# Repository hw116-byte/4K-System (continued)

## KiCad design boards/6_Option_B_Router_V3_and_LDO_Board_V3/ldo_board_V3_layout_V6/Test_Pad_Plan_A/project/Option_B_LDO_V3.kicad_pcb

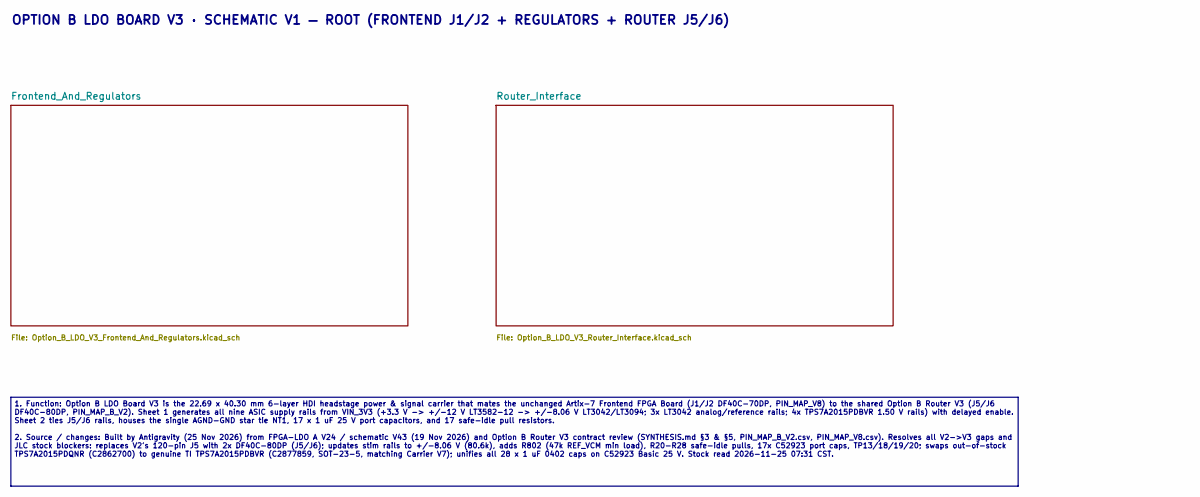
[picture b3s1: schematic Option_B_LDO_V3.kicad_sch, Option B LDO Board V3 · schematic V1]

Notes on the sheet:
1. Function: Option B LDO Board V3 is the 22.69 x 40.30 mm 6-layer HDI headstage power & signal carrier that mates the unchanged Artix-7 Frontend FPGA Board (J1/J2 DF40C-70DP, PIN_MAP_V8) to the shared Option B Router V3 (J5/J6 DF40C-80DP, PIN_MAP_B_V2). Sheet 1 generates all nine ASIC supply rails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
OPTION B LDO BOARD V3 · SCHEMATIC V1 — ROOT (FRONTEND J1/J2 + REGULATORS + ROUTER J5/J6)

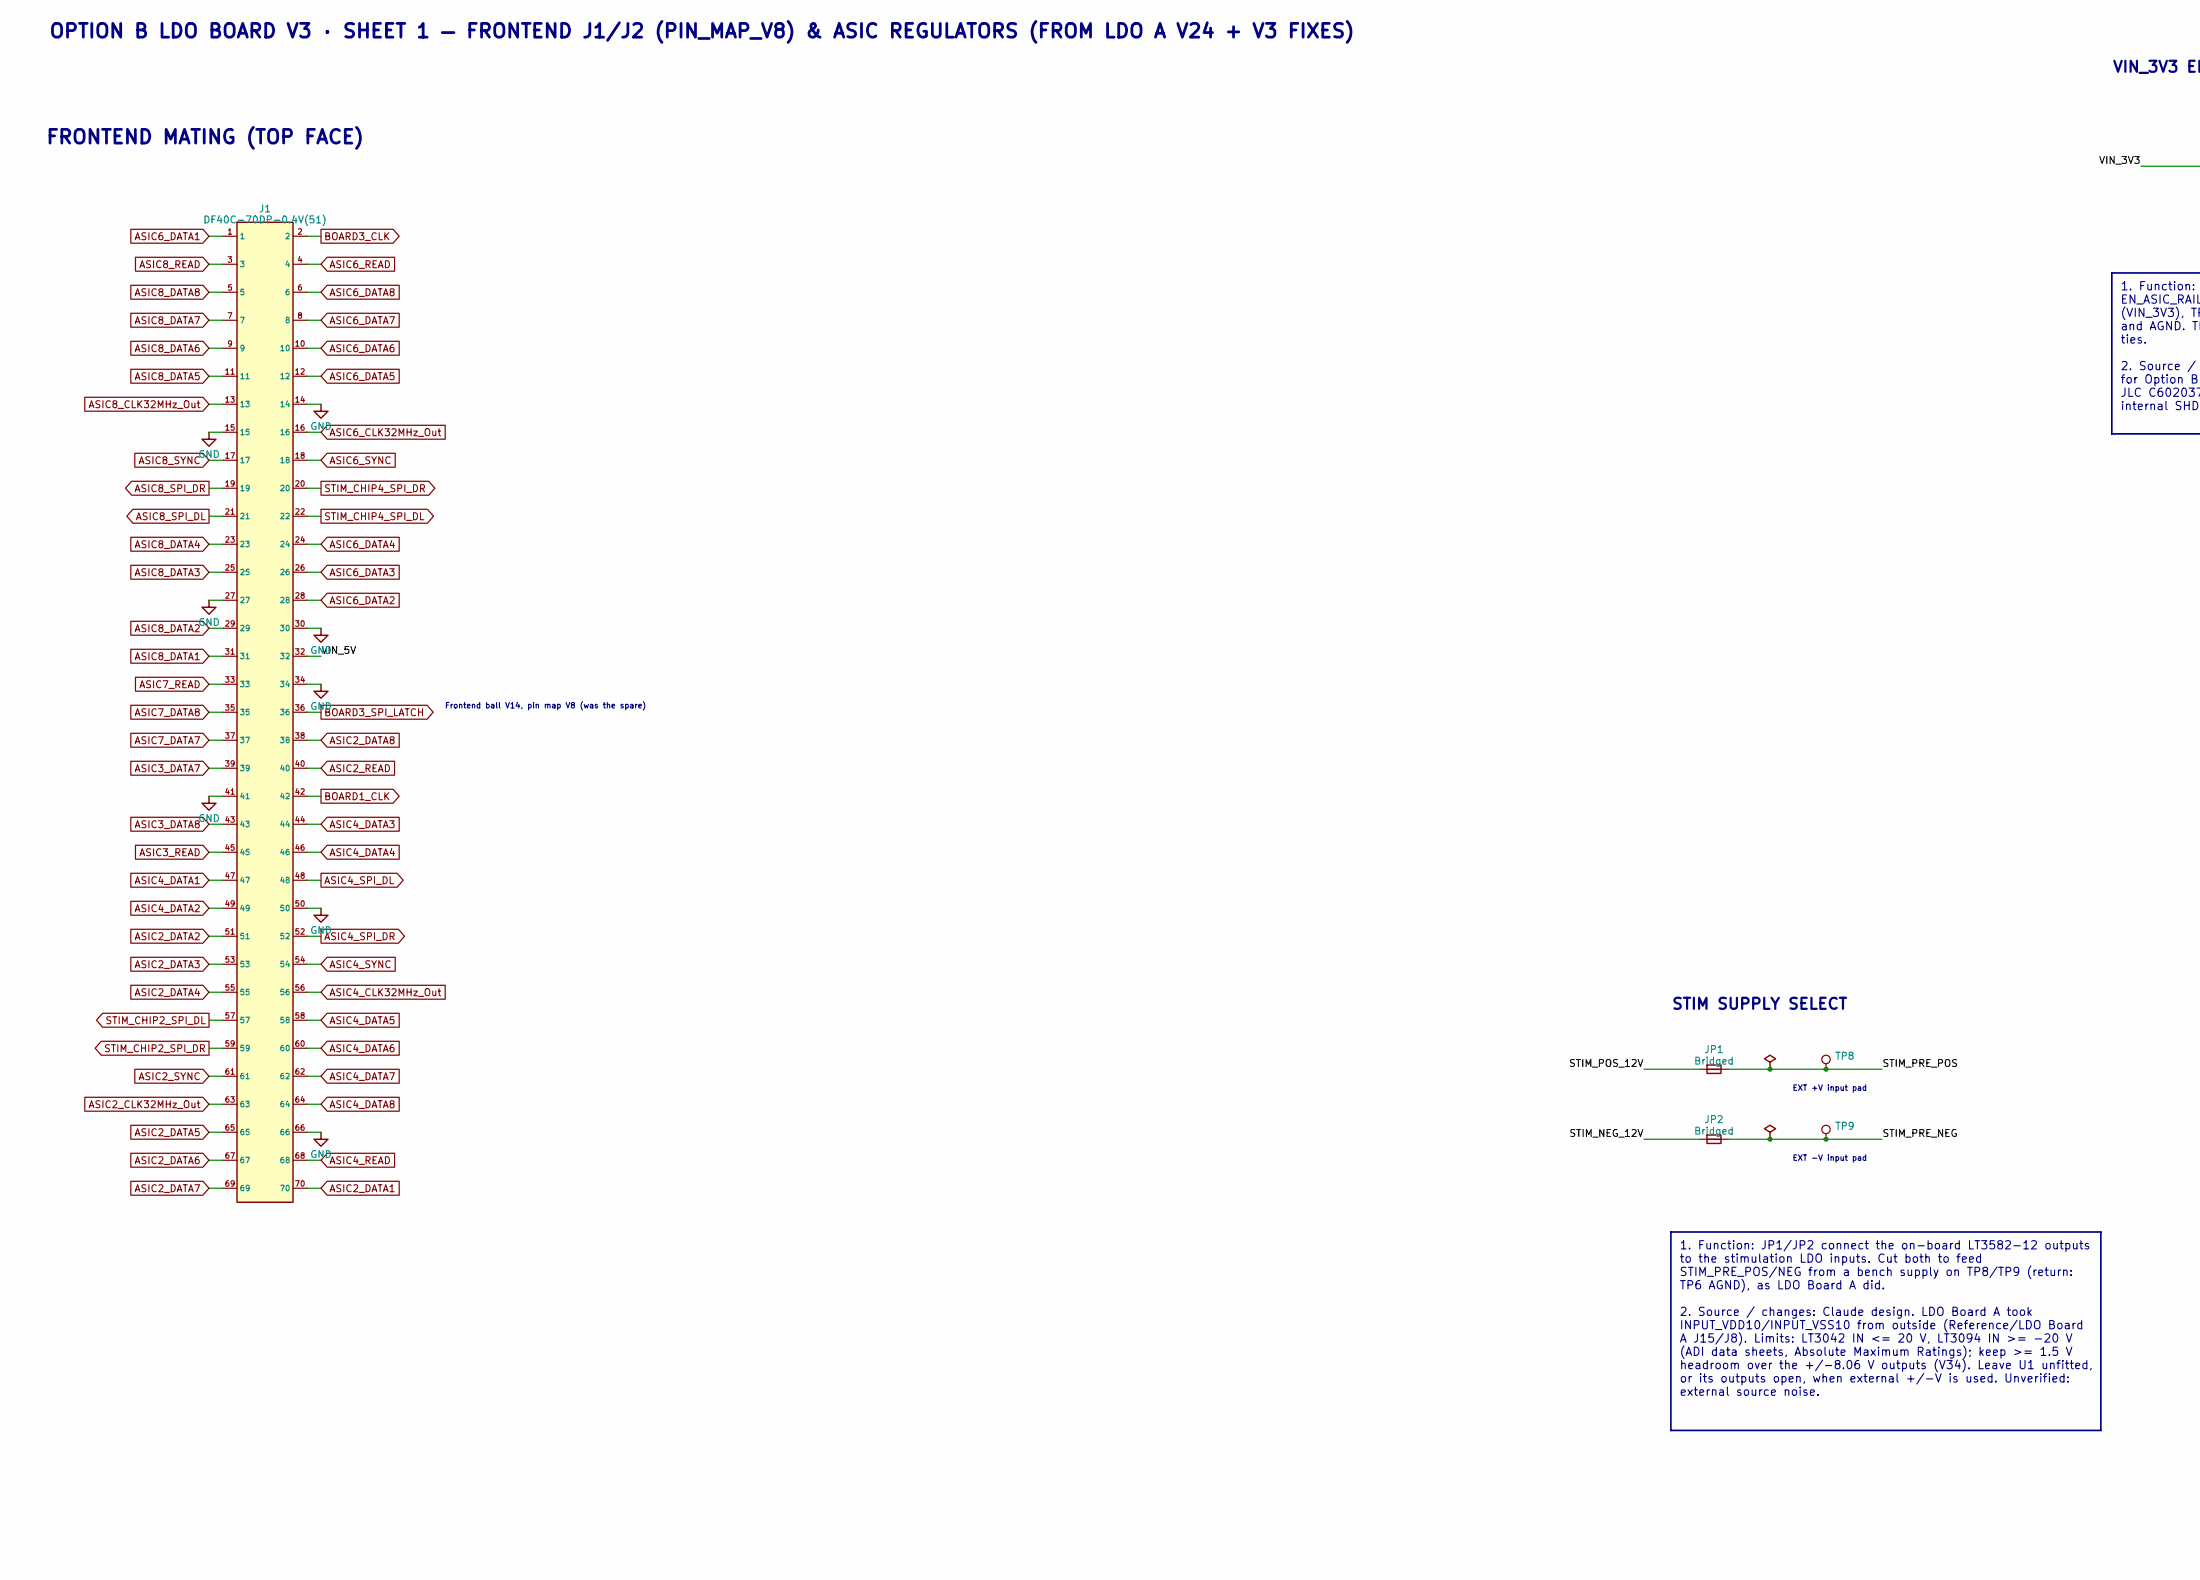
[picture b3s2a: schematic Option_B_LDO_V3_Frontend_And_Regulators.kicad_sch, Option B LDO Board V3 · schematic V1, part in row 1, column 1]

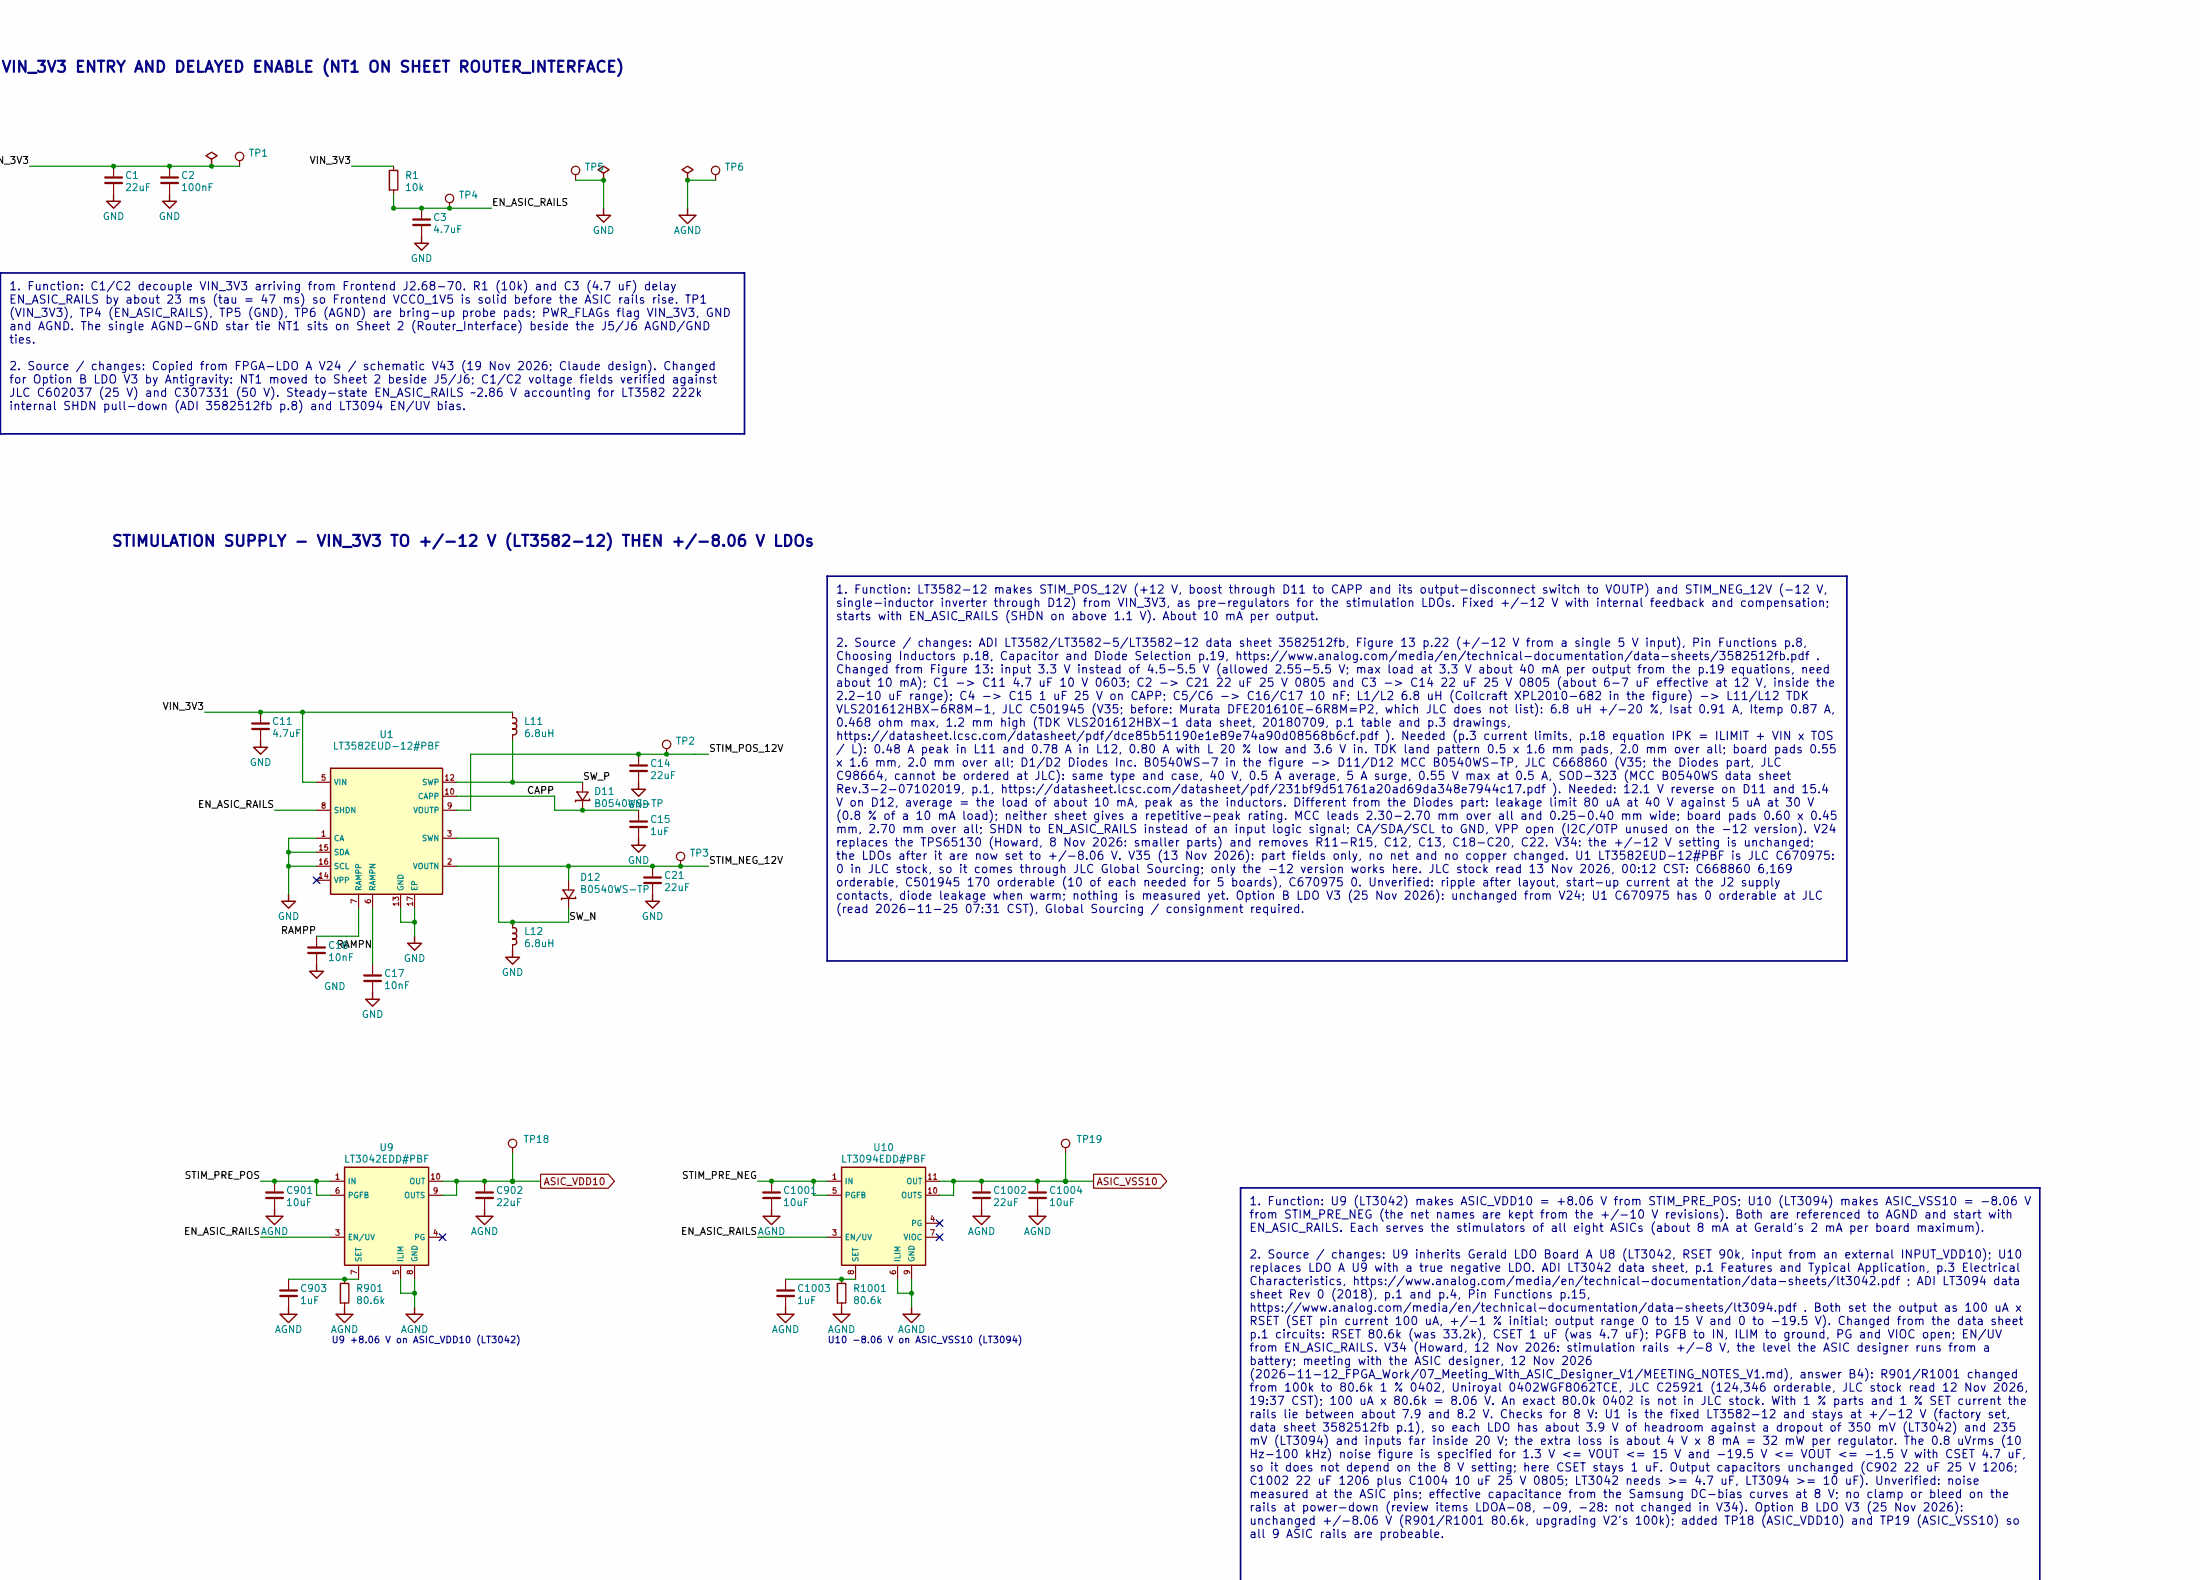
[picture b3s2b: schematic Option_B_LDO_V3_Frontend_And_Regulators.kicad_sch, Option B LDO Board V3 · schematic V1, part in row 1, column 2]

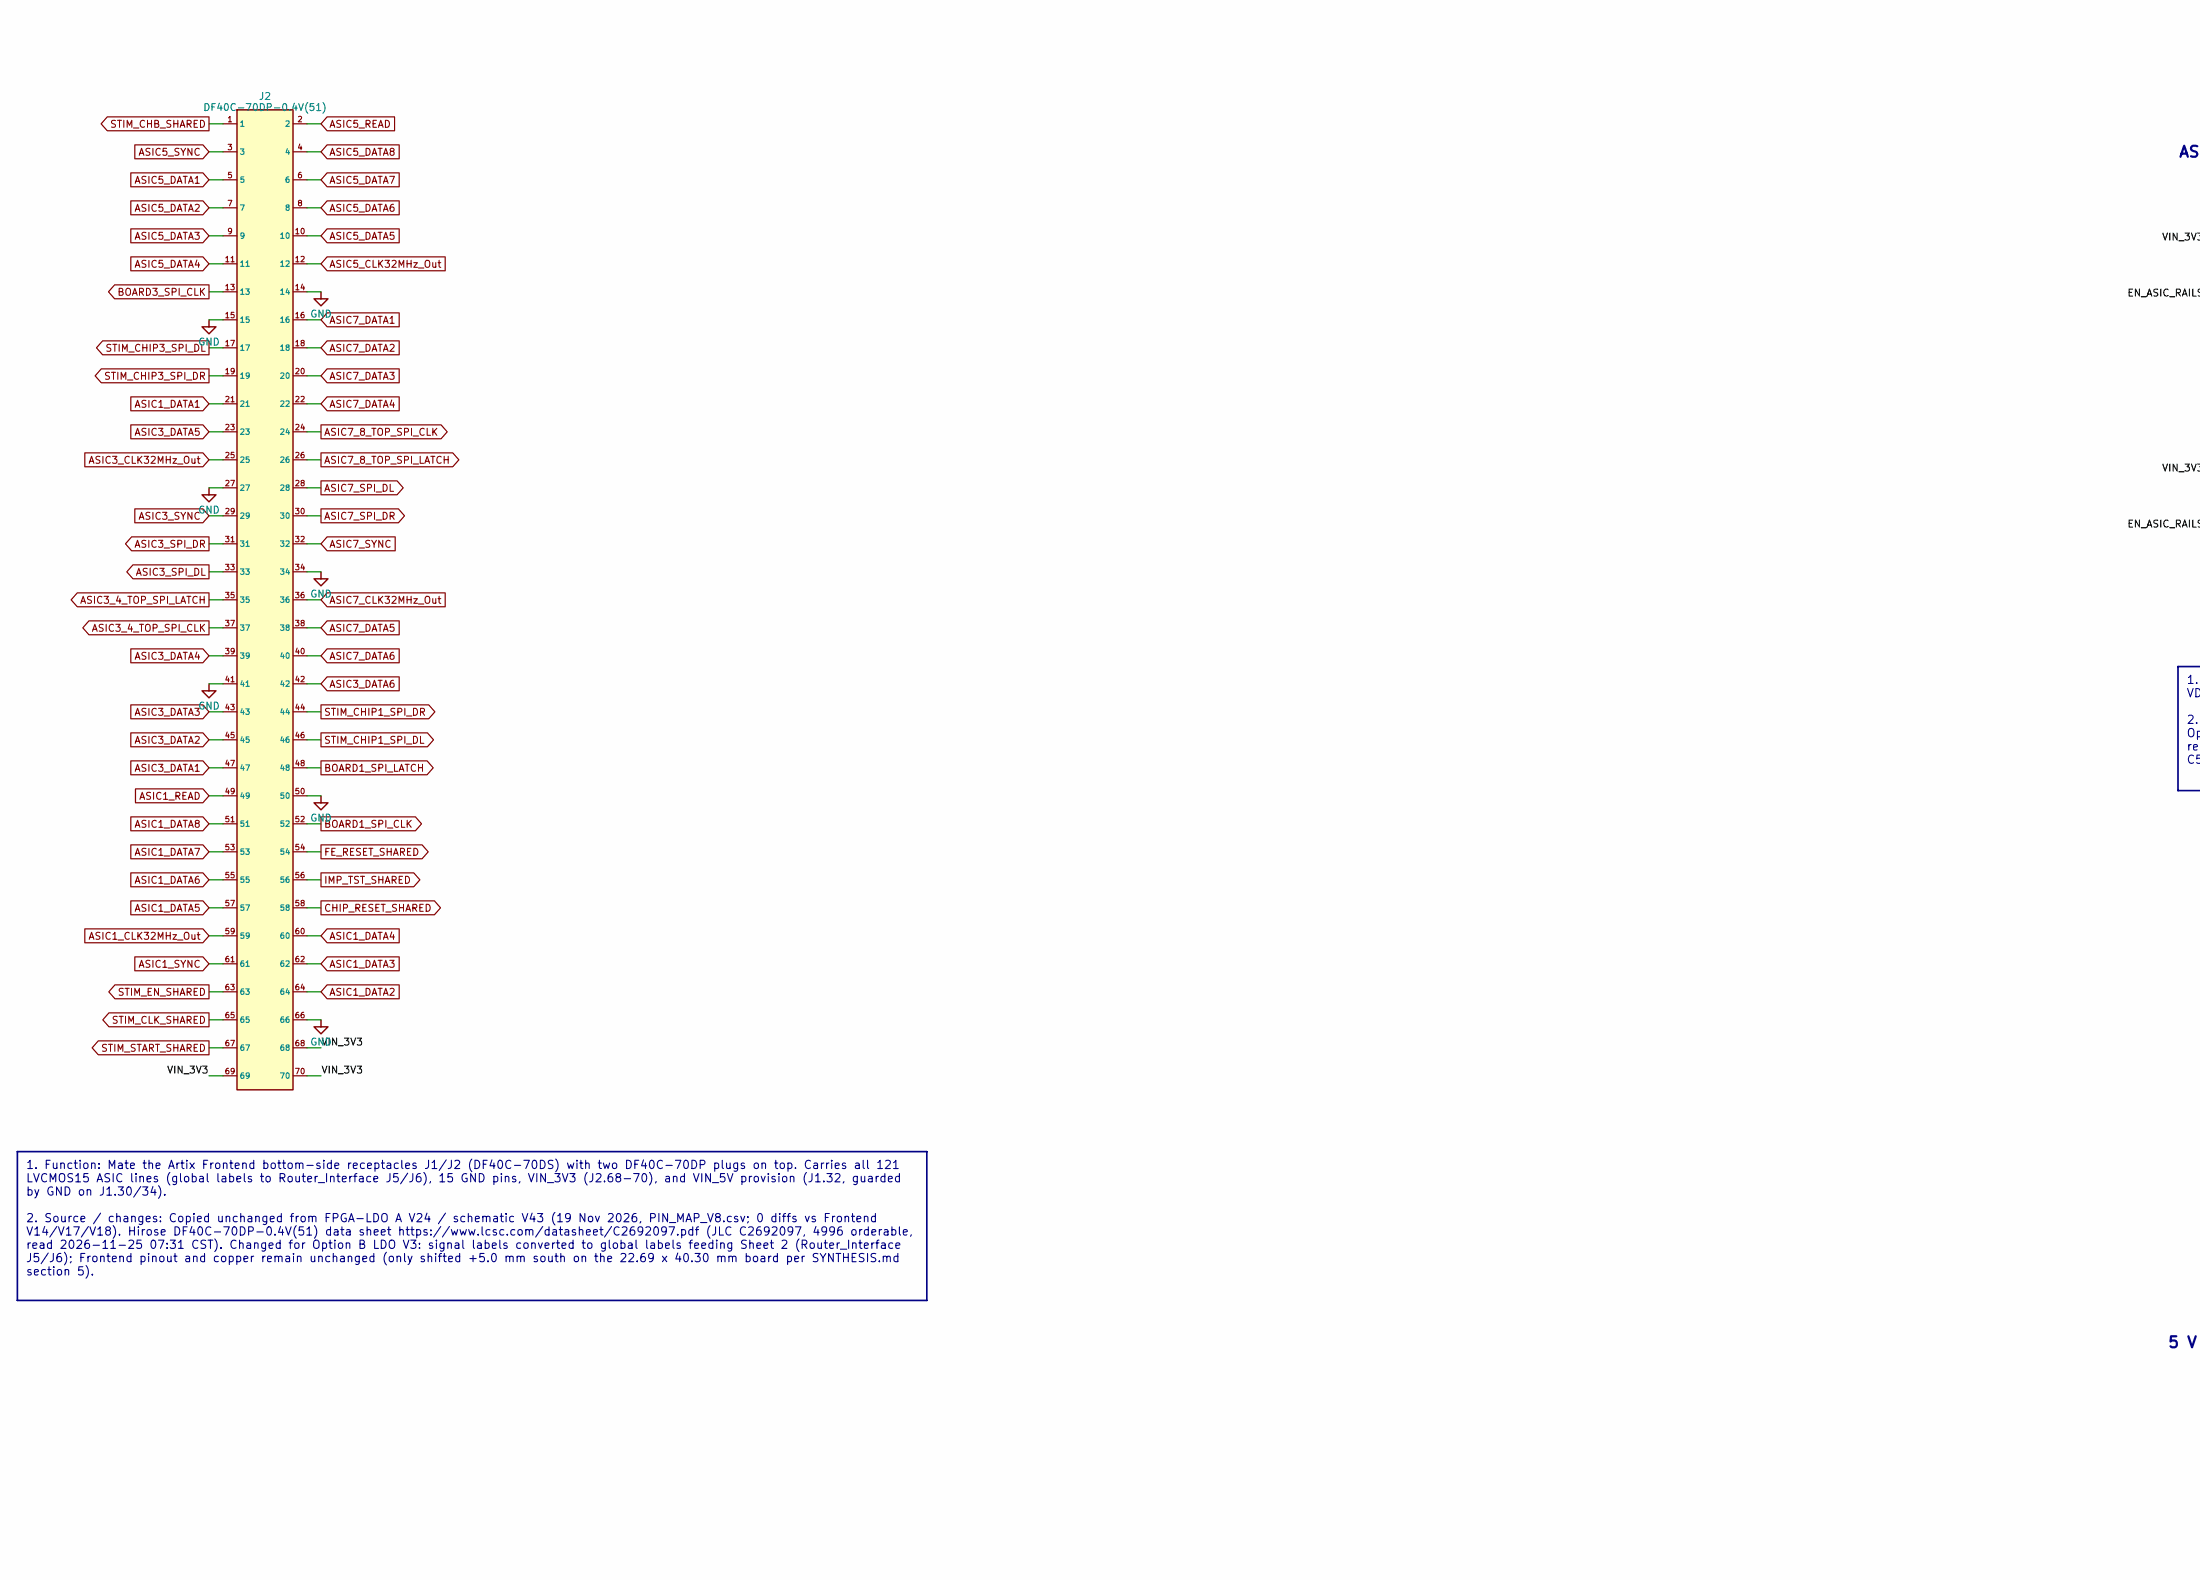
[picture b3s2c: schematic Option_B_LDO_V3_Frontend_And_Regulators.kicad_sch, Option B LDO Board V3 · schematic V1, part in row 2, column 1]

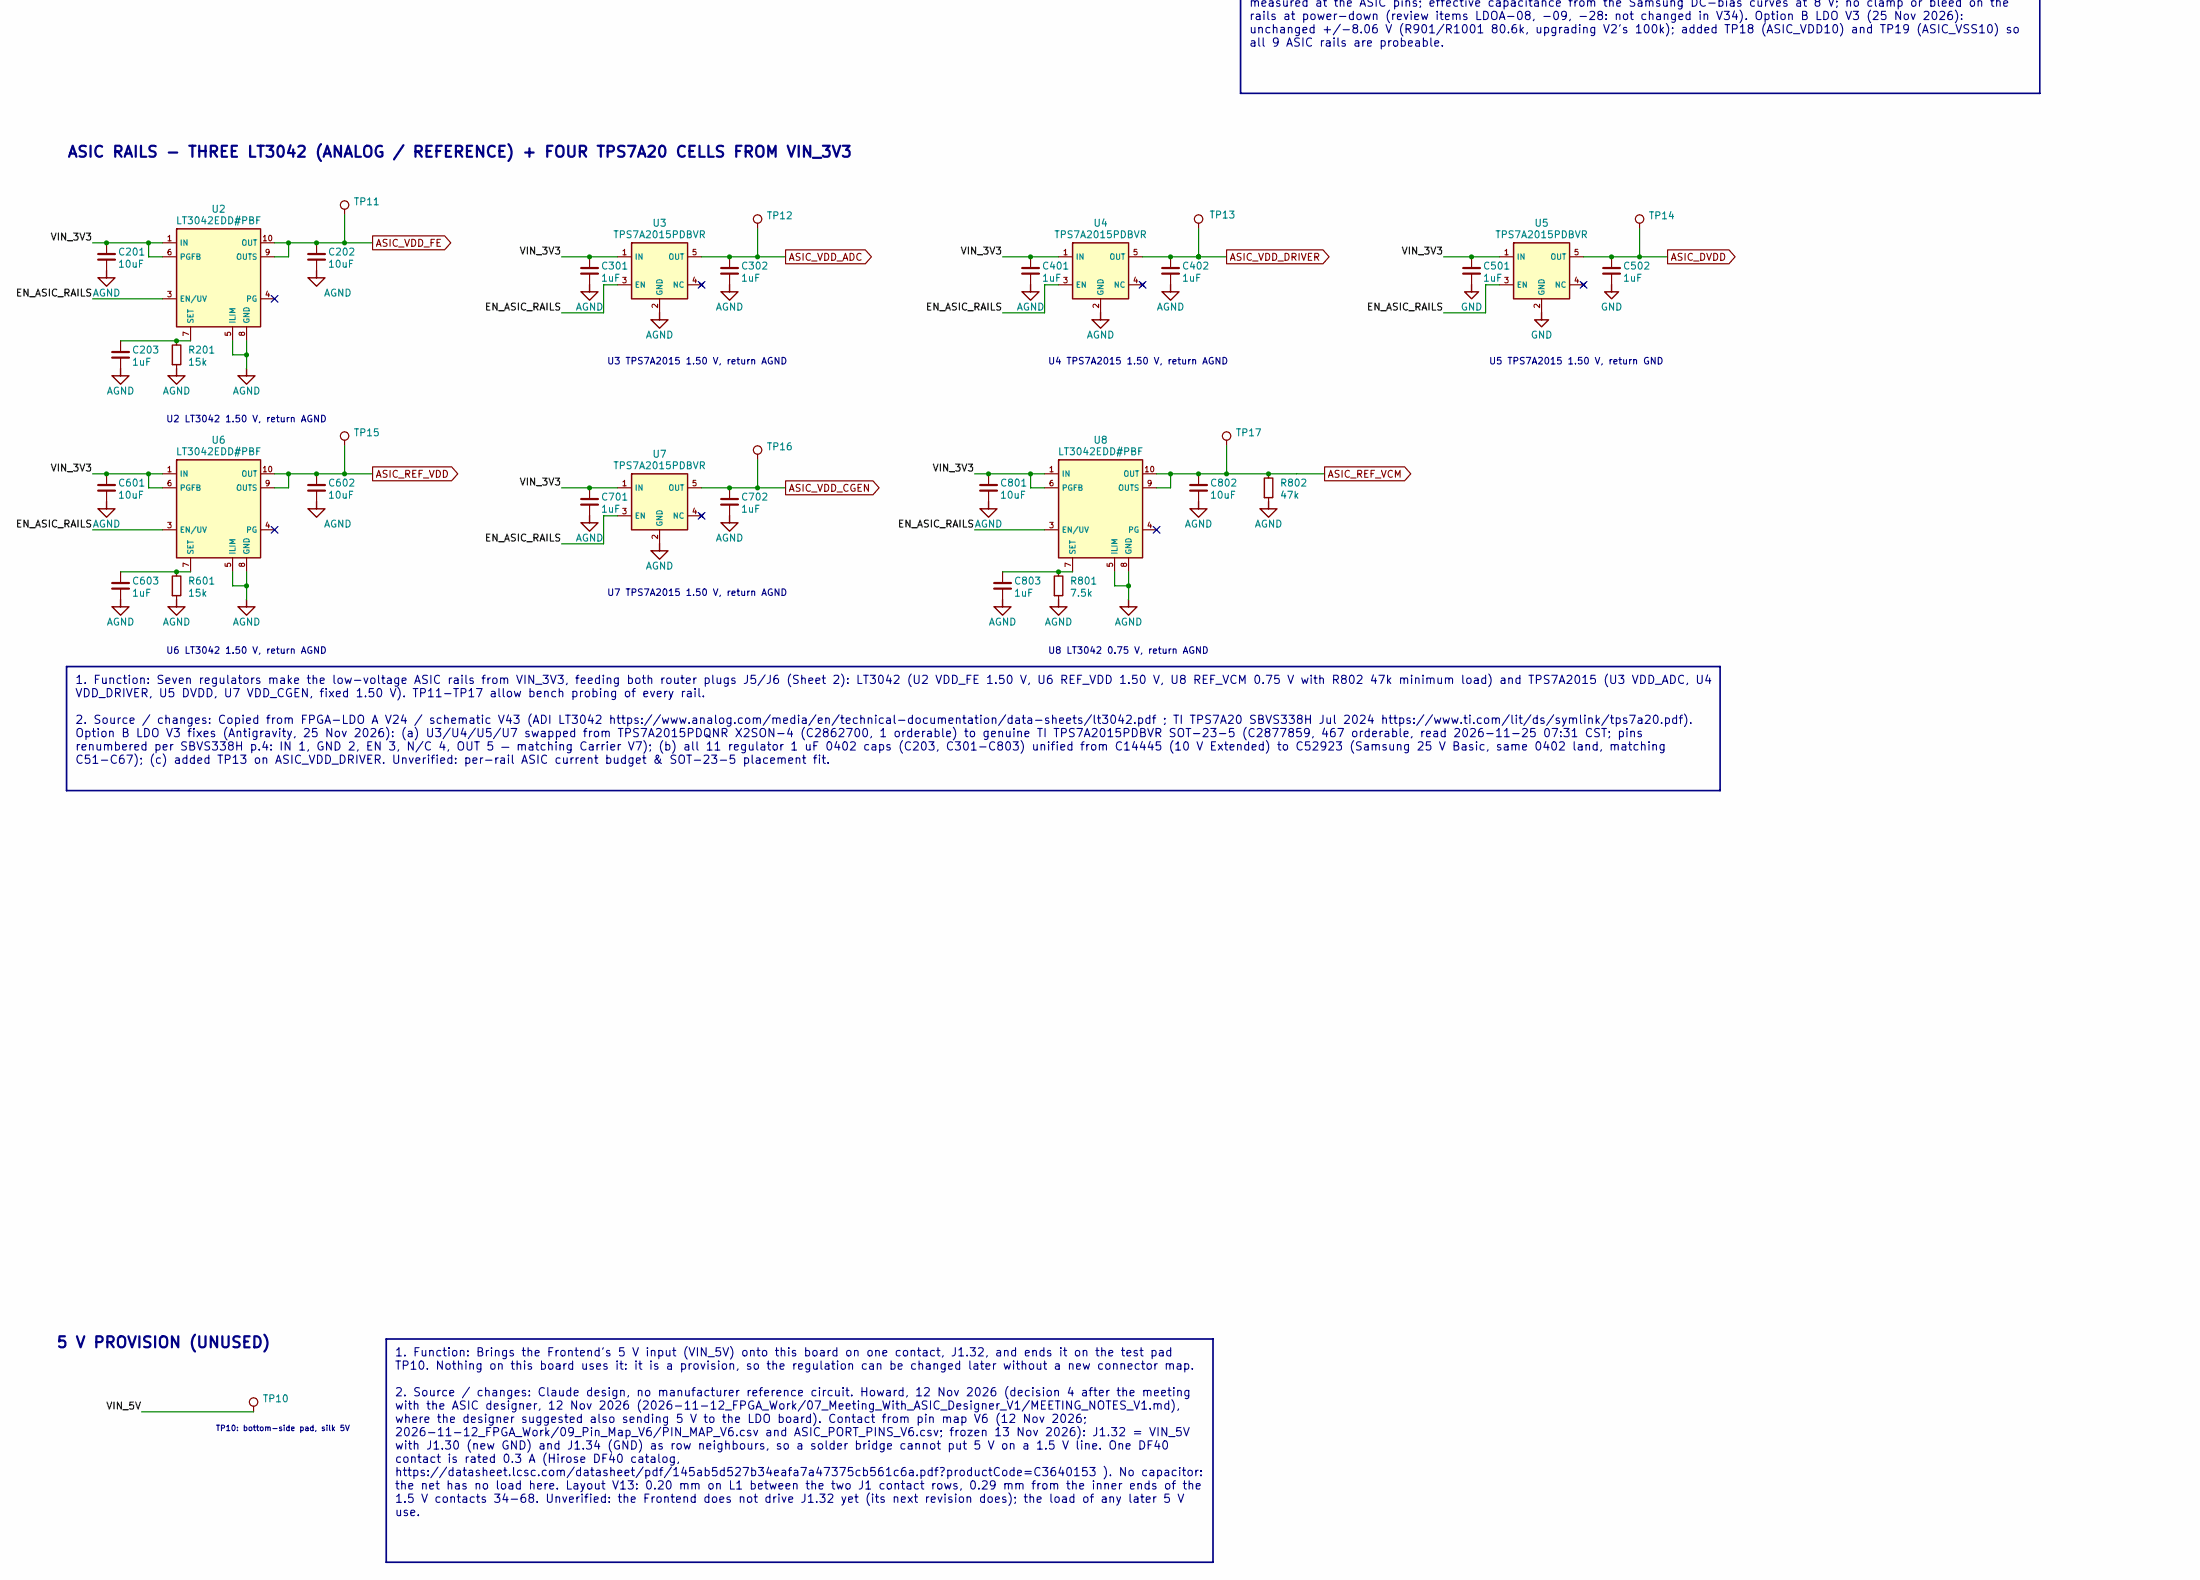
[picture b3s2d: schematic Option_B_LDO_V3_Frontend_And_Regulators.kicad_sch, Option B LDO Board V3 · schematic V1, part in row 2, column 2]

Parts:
C1, C14, C21: 22uF; C_0805_2012Metric; Voltage 25V; MPN Samsung CL21A226MAYNNNE (22uF 25V X5R 0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; LCSC C602037
C2: 100nF; C_0402_1005Metric; Voltage 50V; MPN Samsung CL05B104KB54PNC (100nF 50V X7R 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; LCSC C307331
C3: 4.7uF; C_0603_1608Metric; Voltage 10V; MPN Samsung CL10A475KP8NNNC (4.7uF 10V X5R 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; LCSC C1705
C11: 4.7uF; C_0603_1608Metric; Voltage 10V; LCSC C1705
C15, C903, C1003: 1uF; C_0603_1608Metric; Voltage 25V; MPN Samsung CL10A105KA8NNNC (1uF 25V X5R 06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; LCSC C5673
C16, C17: 10nF; C_0402_1005Metric; Voltage 50V; MPN Samsung CL05B103KB5NNNC (10nF 50V X7R 0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; LCSC C15195
C201, C202, C601, C602, C801, C802: 10uF; C_0603_1608Metric; Voltage 10V; MPN Samsung CL10A106KP8NNNC (10uF 10V X5R 0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; LCSC C19702
C203, C301, C302, C401, C402, C501, C502, C603, C701, C702, C803: 1uF; C_0402_1005Metric; Voltage 25V; MPN Samsung CL05A105KA5NQNC (1 uF 25 V X5R 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; LCSC C52923
C901, C1001, C1004: 10uF; C_0805_2012Metric; Voltage 25V; MPN Samsung CL21A106KAYNNNE (10uF 25V X5R 0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; LCSC C15850
C902, C1002: 22uF; C_1206_3216Metric; Voltage 25V; MPN Samsung CL31A226KAHNNNE (22uF 25V X5R 1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; LCSC C12891
D11, D12: B0540WS-TP; D_SOD-323; MPN MCC B0540WS-TP (40 V 0.5 A SOD-323); LCSC C668860
J1, J2: DF40C-70DP-0.4V(51); Hirose_DF40C-70DP-0.4V_2x35-1MP_P0.4mm; MPN DF40C-70DP-0.4V(51); LCSC C2692097
JP1, JP2: Bridged; SolderJumper-2_P1.3mm_Bridged_RoundedPad1.0x1.5mm
L11, L12: 6.8uH; L_Murata_DFE201610P; MPN TDK VLS201612HBX-6R8M-1 (6.8 uH 20 %, 2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; LCSC C501945
R1: 10k; R_0402_1005Metric; Tolerance 1%; LCSC C25744
R201, R601: 15k; R_0402_1005Metric; Tolerance 1%; MPN UNI-ROYAL 0402WGF1502TCE (15k 1% 0402); LCSC C25756
R801: 7.5k; R_0402_1005Metric; Tolerance 1%; MPN UNI-ROYAL 0402WGF7501TCE (7.5k 1% 0402); LCSC C25918
R802: 47k; R_0402_1005Metric; Tolerance 1%; MPN Uniroyal 0402WGF4702TCE (47k 1% 0402); LCSC C25792
R901, R1001: 80.6k; R_0402_1005Metric; Tolerance 1%; MPN Uniroyal 0402WGF8062TCE (80.6k 1% 0402); LCSC C25921
TP1: VIN_3V3; TestPoint_Pad_D1.0mm_Compact
TP2: STIM_POS_12V; TestPoint_Pad_D1.0mm_Compact
TP3: STIM_NEG_12V; TestPoint_Pad_D1.0mm_Compact
TP4: EN_ASIC_RAILS; TestPoint_Pad_D1.0mm_Compact
TP5: GND; TestPoint_Pad_D1.0mm_Compact
TP6: AGND; TestPoint_Pad_D1.0mm_Compact
TP8: STIM_PRE_POS; TestPoint_Pad_D1.0mm_Compact
TP9: STIM_PRE_NEG; TestPoint_Pad_D1.0mm_Compact
TP10: VIN_5V; TestPoint_Pad_D1.0mm_Compact
TP11: ASIC_VDD_FE; TestPoint_Pad_D0.6mm_Compact
TP12: ASIC_VDD_ADC; TestPoint_Pad_D0.6mm_Compact
TP13: ASIC_VDD_DRIVER; TestPoint_Pad_D1.0mm_Compact
TP14: ASIC_DVDD; TestPoint_Pad_D0.6mm_Compact
TP15: ASIC_REF_VDD; TestPoint_Pad_D0.6mm_Compact
TP16: ASIC_VDD_CGEN; TestPoint_Pad_D0.6mm_Compact
TP17: ASIC_REF_VCM; TestPoint_Pad_D0.6mm_Compact
TP18: ASIC_VDD10; TestPoint_Pad_D1.0mm_Compact
TP19: ASIC_VSS10; TestPoint_Pad_D1.0mm_Compact
U1: LT3582EUD-12#PBF; QFN-16-1EP_3x3mm_P0.5mm_EP1.45x1.45mm; MPN LT3582EUD-12#PBF; LCSC C670975
U2, U6, U8, U9: LT3042EDD#PBF; DFN-10-1EP_3x3mm_P0.5mm_EP1.65x2.38mm; MPN LT3042EDD#TRPBF; LCSC C580010
U3, U4, U5, U7: TPS7A2015PDBVR; SOT-23-5; MPN TPS7A2015PDBVR; LCSC C2877859
U10: LT3094EDD#PBF; DFN-12-1EP_3x3mm_P0.45mm_EP1.65x2.38mm; MPN LT3094EDD#PBF; LCSC C670492

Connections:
/Frontend_And_Regulators/CAPP: C15.1, D11.1 (K), U1.10 (CAPP), U1.11 (CAPP)
/Frontend_And_Regulators/EN_ASIC_RAILS: C3.1, R1.2, TP4.1, U1.8 (SHDN), U2.3 (EN/UV), U3.3 (EN), U4.3 (EN), U5.3 (EN), U6.3 (EN/UV), U7.3 (EN), U8.3 (EN/UV), U9.3 (EN/UV), U10.3 (EN/UV)
/Frontend_And_Regulators/RAMPN: C17.1, U1.6 (RAMPN)
/Frontend_And_Regulators/RAMPP: C16.1, U1.7 (RAMPP)
/Frontend_And_Regulators/STIM_NEG_12V: C21.1, D12.2 (A), JP2.1, TP3.1, U1.2 (VOUTN)
/Frontend_And_Regulators/STIM_POS_12V: C14.1, JP1.1, TP2.1, U1.9 (VOUTP)
/Frontend_And_Regulators/STIM_PRE_NEG: C1001.1, JP2.2, TP9.1, U10.1 (IN), U10.2 (IN), U10.5 (PGFB), U10.13 (IN)
/Frontend_And_Regulators/STIM_PRE_POS: C901.1, JP1.2, TP8.1, U9.1 (IN), U9.2 (IN), U9.6 (PGFB)
/Frontend_And_Regulators/SW_N: D12.1 (K), L12.1, U1.3 (SWN), U1.4 (SWN)
/Frontend_And_Regulators/SW_P: D11.2 (A), L11.2, U1.12 (SWP)
/Frontend_And_Regulators/VIN_3V3: C1.1, C2.1, C11.1, C201.1, C301.1, C401.1, C501.1, C601.1, C701.1, C801.1, J2.68, J2.69, J2.70, L11.1, R1.1, TP1.1, U1.5 (VIN), U2.1 (IN), U2.2 (IN), U2.6 (PGFB), U3.1 (IN), U4.1 (IN), U5.1 (IN), U6.1 (IN), U6.2 (IN), U6.6 (PGFB), U7.1 (IN), U8.1 (IN), U8.2 (IN), U8.6 (PGFB)
/Frontend_And_Regulators/VIN_5V: J1.32, TP10.1
AGND: C201.2, C202.2, C203.2, C301.2, C302.2, C401.2, C402.2, C601.2, C602.2, C603.2, C701.2, C702.2, C801.2, C802.2, C803.2, C901.2, C902.2, C903.2, C1001.2, C1002.2, C1003.2, C1004.2, R201.2, R601.2, R801.2, R802.2, R901.2, R1001.2, TP6.1, U2.5 (ILIM), U2.8 (GND), U2.11 (GND), U3.2 (GND), U4.2 (GND), U6.5 (ILIM), U6.8 (GND), U6.11 (GND), U7.2 (GND), U8.5 (ILIM), U8.8 (GND), U8.11 (GND), U9.5 (ILIM), U9.8 (GND), U9.11 (GND), U10.6 (ILIM), U10.9 (GND); also elsewhere on the board
ASIC1_CLK32MHz_Out: J2.59; also elsewhere on the board
ASIC1_DATA1: J2.21; also elsewhere on the board
ASIC1_DATA2: J2.64; also elsewhere on the board
ASIC1_DATA3: J2.62; also elsewhere on the board
ASIC1_DATA4: J2.60; also elsewhere on the board
ASIC1_DATA5: J2.57; also elsewhere on the board
ASIC1_DATA6: J2.55; also elsewhere on the board
ASIC1_DATA7: J2.53; also elsewhere on the board
ASIC1_DATA8: J2.51; also elsewhere on the board
ASIC1_READ: J2.49; also elsewhere on the board
ASIC1_SYNC: J2.61; also elsewhere on the board
ASIC2_CLK32MHz_Out: J1.63; also elsewhere on the board
ASIC2_DATA1: J1.70; also elsewhere on the board
ASIC2_DATA2: J1.51; also elsewhere on the board
ASIC2_DATA3: J1.53; also elsewhere on the board
ASIC2_DATA4: J1.55; also elsewhere on the board
ASIC2_DATA5: J1.65; also elsewhere on the board
ASIC2_DATA6: J1.67; also elsewhere on the board
ASIC2_DATA7: J1.69; also elsewhere on the board
ASIC2_DATA8: J1.38; also elsewhere on the board
ASIC2_READ: J1.40; also elsewhere on the board
ASIC2_SYNC: J1.61; also elsewhere on the board
ASIC3_4_TOP_SPI_CLK: J2.37; also elsewhere on the board
ASIC3_4_TOP_SPI_LATCH: J2.35; also elsewhere on the board
ASIC3_CLK32MHz_Out: J2.25; also elsewhere on the board
ASIC3_DATA1: J2.47; also elsewhere on the board
ASIC3_DATA2: J2.45; also elsewhere on the board
ASIC3_DATA3: J2.43; also elsewhere on the board
ASIC3_DATA4: J2.39; also elsewhere on the board
ASIC3_DATA5: J2.23; also elsewhere on the board
ASIC3_DATA6: J2.42; also elsewhere on the board
ASIC3_DATA7: J1.39; also elsewhere on the board
ASIC3_DATA8: J1.43; also elsewhere on the board
ASIC3_READ: J1.45; also elsewhere on the board
ASIC3_SPI_DL: J2.33; also elsewhere on the board
ASIC3_SPI_DR: J2.31; also elsewhere on the board
ASIC3_SYNC: J2.29; also elsewhere on the board
ASIC4_CLK32MHz_Out: J1.56; also elsewhere on the board
ASIC4_DATA1: J1.47; also elsewhere on the board
ASIC4_DATA2: J1.49; also elsewhere on the board
ASIC4_DATA3: J1.44; also elsewhere on the board
ASIC4_DATA4: J1.46; also elsewhere on the board
ASIC4_DATA5: J1.58; also elsewhere on the board
ASIC4_DATA6: J1.60; also elsewhere on the board
ASIC4_DATA7: J1.62; also elsewhere on the board
ASIC4_DATA8: J1.64; also elsewhere on the board
ASIC4_READ: J1.68; also elsewhere on the board
ASIC4_SPI_DL: J1.48; also elsewhere on the board
ASIC4_SPI_DR: J1.52; also elsewhere on the board
ASIC4_SYNC: J1.54; also elsewhere on the board
ASIC5_CLK32MHz_Out: J2.12; also elsewhere on the board
ASIC5_DATA1: J2.5; also elsewhere on the board
ASIC5_DATA2: J2.7; also elsewhere on the board
ASIC5_DATA3: J2.9; also elsewhere on the board
ASIC5_DATA4: J2.11; also elsewhere on the board
ASIC5_DATA5: J2.10; also elsewhere on the board
ASIC5_DATA6: J2.8; also elsewhere on the board
ASIC5_DATA7: J2.6; also elsewhere on the board
ASIC5_DATA8: J2.4; also elsewhere on the board
ASIC5_READ: J2.2; also elsewhere on the board
ASIC5_SYNC: J2.3; also elsewhere on the board
ASIC6_CLK32MHz_Out: J1.16; also elsewhere on the board
ASIC6_DATA1: J1.1; also elsewhere on the board
ASIC6_DATA2: J1.28; also elsewhere on the board
ASIC6_DATA3: J1.26; also elsewhere on the board
ASIC6_DATA4: J1.24; also elsewhere on the board
ASIC6_DATA5: J1.12; also elsewhere on the board
ASIC6_DATA6: J1.10; also elsewhere on the board
ASIC6_DATA7: J1.8; also elsewhere on the board
ASIC6_DATA8: J1.6; also elsewhere on the board
ASIC6_READ: J1.4; also elsewhere on the board
ASIC6_SYNC: J1.18; also elsewhere on the board
ASIC7_8_TOP_SPI_CLK: J2.24; also elsewhere on the board
ASIC7_8_TOP_SPI_LATCH: J2.26; also elsewhere on the board
ASIC7_CLK32MHz_Out: J2.36; also elsewhere on the board
ASIC7_DATA1: J2.16; also elsewhere on the board
ASIC7_DATA2: J2.18; also elsewhere on the board
ASIC7_DATA3: J2.20; also elsewhere on the board
ASIC7_DATA4: J2.22; also elsewhere on the board
ASIC7_DATA5: J2.38; also elsewhere on the board
ASIC7_DATA6: J2.40; also elsewhere on the board
ASIC7_DATA7: J1.37; also elsewhere on the board
ASIC7_DATA8: J1.35; also elsewhere on the board
ASIC7_READ: J1.33; also elsewhere on the board
ASIC7_SPI_DL: J2.28; also elsewhere on the board
ASIC7_SPI_DR: J2.30; also elsewhere on the board
ASIC7_SYNC: J2.32; also elsewhere on the board
ASIC8_CLK32MHz_Out: J1.13; also elsewhere on the board
ASIC8_DATA1: J1.31; also elsewhere on the board
ASIC8_DATA2: J1.29; also elsewhere on the board
ASIC8_DATA3: J1.25; also elsewhere on the board
ASIC8_DATA4: J1.23; also elsewhere on the board
ASIC8_DATA5: J1.11; also elsewhere on the board
ASIC8_DATA6: J1.9; also elsewhere on the board
ASIC8_DATA7: J1.7; also elsewhere on the board
ASIC8_DATA8: J1.5; also elsewhere on the board
ASIC8_READ: J1.3; also elsewhere on the board
ASIC8_SPI_DL: J1.21; also elsewhere on the board
ASIC8_SPI_DR: J1.19; also elsewhere on the board
ASIC8_SYNC: J1.17; also elsewhere on the board
ASIC_DVDD: C502.1, TP14.1, U5.5 (OUT); also elsewhere on the board
ASIC_REF_VCM: C802.1, R802.1, TP17.1, U8.9 (OUTS), U8.10 (OUT); also elsewhere on the board
ASIC_REF_VDD: C602.1, TP15.1, U6.9 (OUTS), U6.10 (OUT); also elsewhere on the board
ASIC_VDD10: C902.1, TP18.1, U9.9 (OUTS), U9.10 (OUT); also elsewhere on the board
ASIC_VDD_ADC: C302.1, TP12.1, U3.5 (OUT); also elsewhere on the board
ASIC_VDD_CGEN: C702.1, TP16.1, U7.5 (OUT); also elsewhere on the board
ASIC_VDD_DRIVER: C402.1, TP13.1, U4.5 (OUT); also elsewhere on the board
ASIC_VDD_FE: C202.1, TP11.1, U2.9 (OUTS), U2.10 (OUT); also elsewhere on the board
ASIC_VSS10: C1002.1, C1004.1, TP19.1, U10.10 (OUTS), U10.11 (OUT), U10.12 (OUT); also elsewhere on the board
BOARD1_CLK: J1.42; also elsewhere on the board
BOARD1_SPI_CLK: J2.52; also elsewhere on the board
BOARD1_SPI_LATCH: J2.48; also elsewhere on the board
BOARD3_CLK: J1.2; also elsewhere on the board
BOARD3_SPI_CLK: J2.13; also elsewhere on the board
BOARD3_SPI_LATCH: J1.36; also elsewhere on the board
CHIP_RESET_SHARED: J2.58; also elsewhere on the board
FE_RESET_SHARED: J2.54; also elsewhere on the board
GND: C1.2, C2.2, C3.2, C11.2, C14.2, C15.2, C16.2, C17.2, C21.2, C501.2, C502.2, J1.14, J1.15, J1.27, J1.30, J1.34, J1.41, J1.50, J1.66, J2.14, J2.15, J2.27, J2.34, J2.41, J2.50, J2.66, L12.2, TP5.1, U1.1 (CA), U1.13 (GND), U1.15 (SDA), U1.16 (SCL), U1.17 (EP), U5.2 (GND); also elsewhere on the board
IMP_TST_SHARED: J2.56; also elsewhere on the board
unnamed: C203.1, R201.1, U2.7 (SET)
unnamed: C603.1, R601.1, U6.7 (SET)
unnamed: C803.1, R801.1, U8.7 (SET)
unnamed: C903.1, R901.1, U9.7 (SET)
unnamed: C1003.1, R1001.1, U10.8 (SET)
STIM_CHB_SHARED: J2.1; also elsewhere on the board
STIM_CHIP1_SPI_DL: J2.46; also elsewhere on the board
STIM_CHIP1_SPI_DR: J2.44; also elsewhere on the board
STIM_CHIP2_SPI_DL: J1.57; also elsewhere on the board
STIM_CHIP2_SPI_DR: J1.59; also elsewhere on the board
STIM_CHIP3_SPI_DL: J2.17; also elsewhere on the board
STIM_CHIP3_SPI_DR: J2.19; also elsewhere on the board
STIM_CHIP4_SPI_DL: J1.22; also elsewhere on the board
STIM_CHIP4_SPI_DR: J1.20; also elsewhere on the board
STIM_CLK_SHARED: J2.65; also elsewhere on the board
STIM_EN_SHARED: J2.63; also elsewhere on the board
STIM_START_SHARED: J2.67; also elsewhere on the board

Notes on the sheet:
Frontend ball V14, pin map V8 (was the spare)
FRONTEND MATING (TOP FACE)
1. Function: Mate the Artix Frontend bottom-side receptacles J1/J2 (DF40C-70DS) with two DF40C-70DP plugs on top. Carries all 121 LVCMOS15 ASIC lines (global labels to Router_Interface J5/J6), 15 GND pins, VIN_3V3 (J2.68-70), and VIN_5V provision (J1.32, guarded by GND on J1.30/34). 2. Source / cha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
ASIC RAILS - THREE LT3042 (ANALOG / REFERENCE) + FOUR TPS7A20 CELLS FROM VIN_3V3
U2 LT3042 1.50 V, return AGND
U3 TPS7A2015 1.50 V, return AGND
U4 TPS7A2015 1.50 V, return AGND
U5 TPS7A2015 1.50 V, return GND
U6 LT3042 1.50 V, return AGND
U7 TPS7A2015 1.50 V, return AGND
U8 LT3042 0.75 V, return AGND
1. Function: Seven regulators make the low-voltage ASIC rails from VIN_3V3, feeding both router plugs J5/J6 (Sheet 2): LT3042 (U2 VDD_FE 1.50 V, U6 REF_VDD 1.50 V, U8 REF_VCM 0.75 V with R802 47k minimum load) and TPS7A2015 (U3 VDD_ADC, U4 VDD_DRIVER, U5 DVDD, U7 VDD_CGEN, fixed 1.50 V). TP11-TP17 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
STIMULATION SUPPLY - VIN_3V3 TO +/-12 V (LT3582-12) THEN +/-8.06 V LDOs
1. Function: LT3582-12 makes STIM_POS_12V (+12 V, boost through D11 to CAPP and its output-disconnect switch to VOUTP) and STIM_NEG_12V (-12 V, single-inductor inverter through D12) from VIN_3V3, as pre-regulators for the stimulation LDOs. Fixed +/-12 V with internal feedback and compensation; star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
U9 +8.06 V on ASIC_VDD10 (LT3042)
U10 -8.06 V on ASIC_VSS10 (LT3094)
1. Function: U9 (LT3042) makes ASIC_VDD10 = +8.06 V from STIM_PRE_POS; U10 (LT3094) makes ASIC_VSS10 = -8.06 V from STIM_PRE_NEG (the net names are kept from the +/-10 V revisions). Both are referenced to AGND and start with EN_ASIC_RAILS. Each serves the stimulators of all eight ASICs (about 8 mA 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
STIM SUPPLY SELECT
EXT +V input pad
EXT -V input pad
1. Function: JP1/JP2 connect the on-board LT3582-12 outputs to the stimulation LDO inputs. Cut both to feed STIM_PRE_POS/NEG from a bench supply on TP8/TP9 (return: TP6 AGND), as LDO Board A did. 2. Source / changes: Claude design. LDO Board A took INPUT_VDD10/INPUT_VSS10 from outside (Reference/LD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
VIN_3V3 ENTRY AND DELAYED ENABLE (NT1 ON SHEET ROUTER_INTERFACE)
1. Function: C1/C2 decouple VIN_3V3 arriving from Frontend J2.68-70. R1 (10k) and C3 (4.7 uF) delay EN_ASIC_RAILS by about 23 ms (tau = 47 ms) so Frontend VCCO_1V5 is solid before the ASIC rails rise. TP1 (VIN_3V3), TP4 (EN_ASIC_RAILS), TP5 (GND), TP6 (AGND) are bring-up probe pads; PWR_FLAGs flag 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
5 V PROVISION (UNUSED)
TP10: bottom-side pad, silk 5V
1. Function: Brings the Frontend's 5 V input (VIN_5V) onto this board on one contact, J1.32, and ends it on the test pad TP10. Nothing on this board uses it: it is a provision, so the regulation can be changed later without a new connector map. 2. Source / changes: Claude design, no manufacturer re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
OPTION B LDO BOARD V3 · SHEET 1 — FRONTEND J1/J2 (PIN_MAP_V8) & ASIC REGULATORS (FROM LDO A V24 + V3 FIXES)
